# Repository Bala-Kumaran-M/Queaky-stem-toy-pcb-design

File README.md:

# Queaky-stem-toy-pcb-design
A compact PCB designed for a Squeaky Stem Toy using KiCad.

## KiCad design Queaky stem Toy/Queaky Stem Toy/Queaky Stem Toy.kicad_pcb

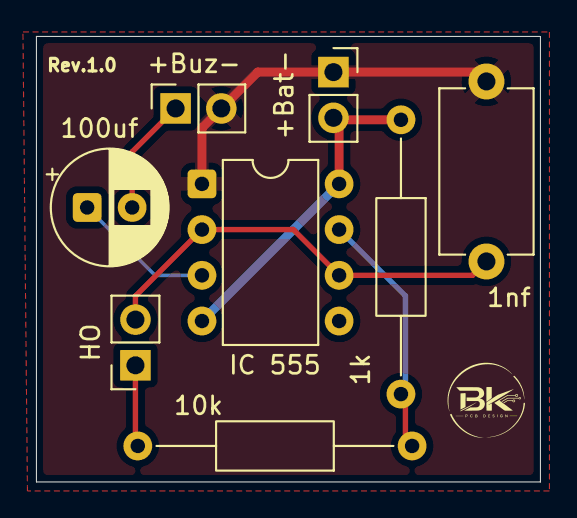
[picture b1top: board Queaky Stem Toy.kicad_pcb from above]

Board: 2 copper layers, 28.0 x 24.8 mm, 8 parts (0 on the bottom side), 7 nets.

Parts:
1k: 1k; R_Axial_DIN0207_L6.3mm_D2.5mm_P15.24mm_Horizontal
1nf: 1nf; C_Disc_D9.0mm_W5.0mm_P10.00mm
10k: 10k; R_Axial_DIN0207_L6.3mm_D2.5mm_P15.24mm_Horizontal
100uf: 100uf; CP_Radial_D6.3mm_P2.50mm
+Bat-: Battery; PinSocket_1x02_P2.54mm_Vertical
+Buz-: Buzzer; PinSocket_1x02_P2.54mm_Vertical
HO: hoomansout; PinSocket_1x02_P2.54mm_Vertical
IC 555: NE555P; DIP-8_W7.62mm

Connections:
/Dis: 1k.2, 10k.1, IC 555.7 (DISCH)
/Out: 100uf.1, IC 555.3 (OUT)
/TR: 1nf.1, HO.2, IC 555.2 (TRIG), IC 555.6 (THRES)
GND: 1nf.2, +Bat-.1, +Buz-.2, IC 555.1 (GND)
unnamed: 100uf.2, +Buz-.1
unnamed: 10k.2, HO.1
VCC: 1k.1, +Bat-.2, IC 555.4 (~RST), IC 555.8 (VCC)
